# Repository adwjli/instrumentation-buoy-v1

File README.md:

# Instrumentation Buoy Data Logger

## Introduction

The client which I worked with in this project was working on a new concept to grow seaweed at an industrial scale (approximately 100km by 100km) in deep ocean waters tens of kilometres offshore. The seaweed plantation is kept afloat using buoys. One of the biggest challenge the client wanted to solve was how to keep the water near the surface of the ocean oxygenated to allow seaweed to grow. One idea was to use the motion of ocean waves to generate compressed air, which can be harnessed to pump air into the water to keep it oxygenated.

To aid in understanding how compressed air can be generated from ocean waves, a Instrumentation Buoy Data Logger was designed to measure various ocean metrics and record the data to a microSD card. The data logger had the following capabilities:
- Can measure water level and depth relative to the buoy.
- Can measure accelerations in all three spatial dimensions.
- Allows two pressure sensors to be connected to the board (via connectors located on the PCB)
- Designed to be completely solar powered. It is powered by an array of solar panels and a rechargeable 18650 Li-ion battery.
- A microSD card is used for data storage, but data transfer is done completely wirelessly using a XBee wireless module. The XBee module also allows over the air firmware updates. The solar-power and wireless capabilities of the data logger are necessary as the electronics will be permanently sealed away inside the buoy to ensure the electronics compartment is water-tight.

The data logger consists of two PCB assemblies sandwiched together. The smaller board is the Main Board. It contains the microcontroller, wireless module, and other digital electronics. The larger board is the Power Board which contains all the power electronics for solar charging. The entire PCB assembly is designed to be mounted in a prototype buoy, and deployed in the ocean to collect data.

The client has agreed to open source the designs.

## Gallery

## PCB Assemblies

## PCB Flats

## Copper Layers

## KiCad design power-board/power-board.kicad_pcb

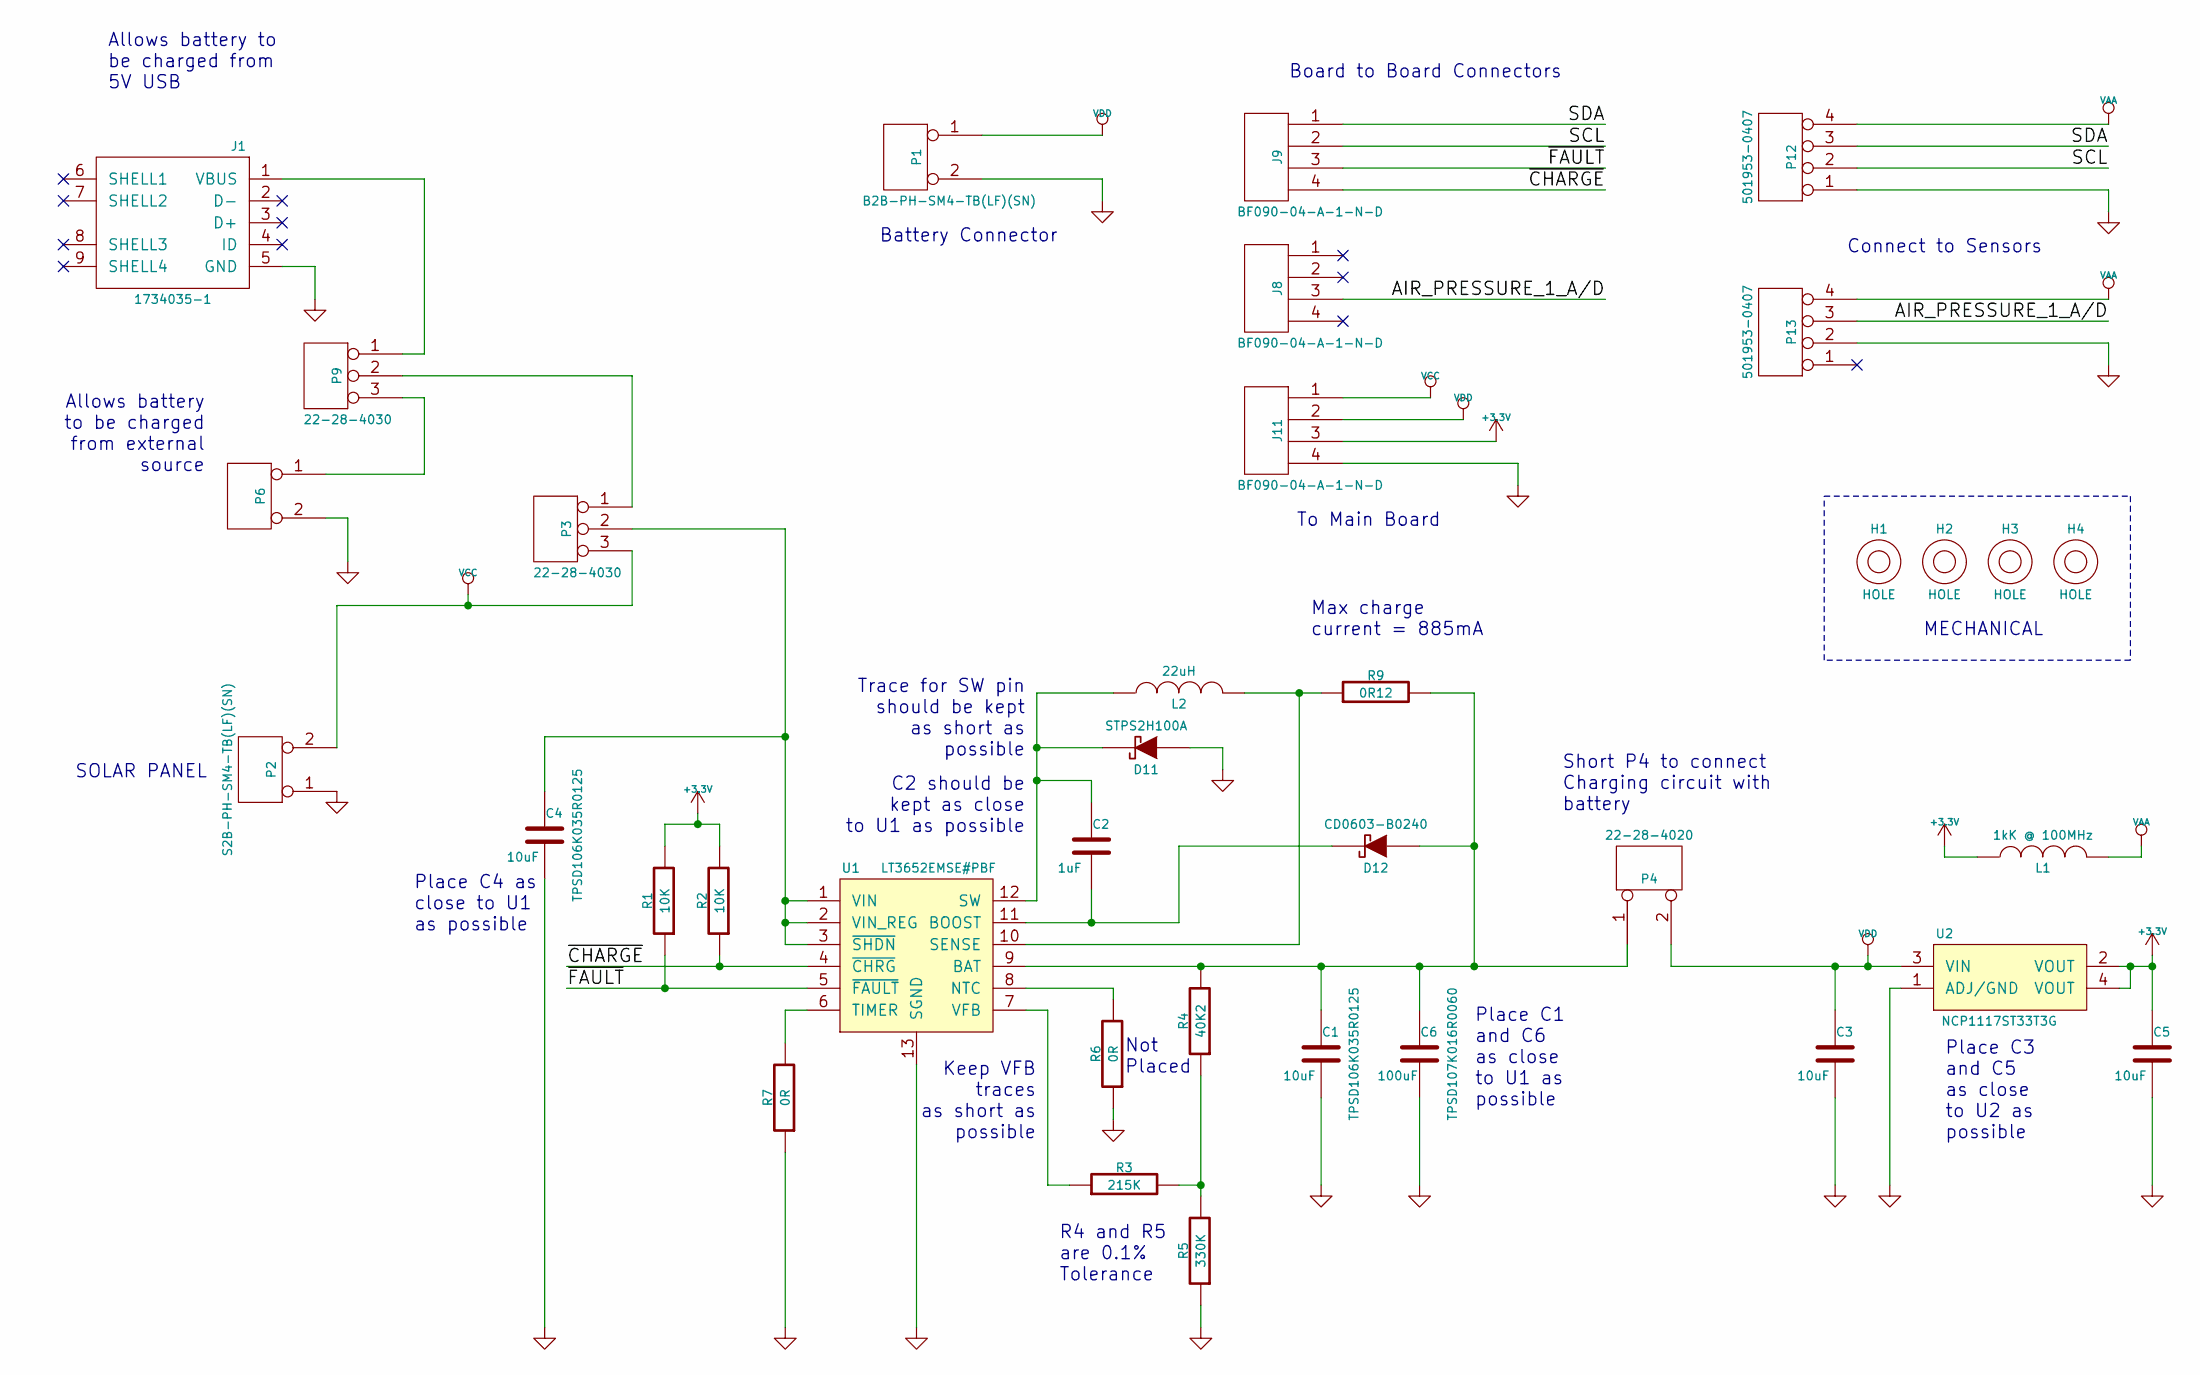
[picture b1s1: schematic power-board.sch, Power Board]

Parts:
C1, C4: ECS00053; EC2917; Manfacturer Part Number TPSD106K035R0125
C2: ECS00052; EC0603_C; Manfacturer Part Number GRM188R61H105KAALD
C3, C5: ECS00050; EC0805; Manfacturer Part Number GRM21BR61A106KE19L
C6: ECS00054; EC2917; Manfacturer Part Number TPSD107K016R0060
D11: ECS00095; ECDO-214AC(SMA); Manufacturer Part Number STPS2H100A
D12: ECS00037; EC0603_DIODE; Manufacturer Part Number CD0603-B0240
H1, H2, H3, H4: HOLE; HOLE_3.0MM
J1: ECS00066; ECUSBMINIB; Manufacturer Part Number 1734035-1
J8, J9, J11: ECS00059; ECS00059F; Manufacturer Part Number BF090-04-A-1-N-D
L1: ECS00074; EC0603_L; Manufacturer Part Number BLM18TG102TN1D
L2: ECS00071; ECS00071F; Manufacturer Part Number 46223C
P1, P6: ECS00067; ECS00067F; Manufacturer Part Number B2B-PH-SM4-TB(LF)(SN)
P2: ECS00007; ECS00007F; Manufacturer Part Number S2B-PH-SM4-TB(LF)(SN)
P3, P9: ECS00013; ECS00013F; Manufacturer Part Number 22-28-4030
P4: ECS00004; ECS00004F; Manufacturer Part Number 22-28-4020
P12, P13: ECS00068; ECS00068F; Manufacturer Part Number 501953-0407
R1, R2: ECS00045; EC0603; Manufacturer Part Number ERJ3GEYJ103V
R3: ECS00046; EC0603; Manufacturer Part Number ERJ3EKF2153V
R4: ECS00048; EC0603; Manufacturer Part Number ERA3ARB4022V
R5: ECS00047; EC0603; Manufacturer Part Number ERJ3EKF3303V
R6, R7: ECS00058; EC0603; Manufacturer Part Number ERJ3GEY0R00V
R9: ECS00055; EC1206; Manufacturer Part Number CRL1206-FW-R120ELF
U1: ECS00043; ECMSOP-12D; Manufacturer Part Number LT3652EMSE#PBF
U2: ECS00036; ECSOT223; Manufacturer Part Number NCP1117ST33T3G

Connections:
+3V3: C5.1, J11.3, L1.1, R1.2, R2.2, U2.2 (VOUT), U2.4 (VOUT)
/AIR_PRESSURE_1_A/D: J8.3, P13.3
/SCL: J9.2, P12.2
/SDA: J9.1, P12.3
/~CHARGE: J9.4, R2.1, U1.4 (~CHRG)
/~FAULT: J9.3, R1.1, U1.5 (~FAULT)
GND: C1.2, C3.2, C4.2, C5.2, C6.2, D11.1 (A), J1.5 (GND), J11.4, P1.2 (PM), P2.1, P6.2 (PM), P12.1, P13.2, R5.1, R6.1, R7.1, U1.13 (SGND), U2.1 (ADJ/GND)
unnamed: C1.1, C6.1, D12.1 (A), P4.1, R4.2, R9.2, U1.9 (BAT)
unnamed: C2.1, D11.2 (K), L2.1, U1.12 (SW)
unnamed: C2.2, D12.2 (K), U1.11 (BOOST)
unnamed: C4.1, P3.2 (PM), U1.1 (VIN), U1.2 (VIN_REG), U1.3 (~SHDN)
unnamed: J1.1 (VBUS), P9.1
unnamed: L2.2, R9.1, U1.10 (SENSE)
unnamed: P3.1, P9.2 (PM)
unnamed: P6.1, P9.3
unnamed: R3.1, U1.7 (VFB)
unnamed: R3.2, R4.1, R5.2
unnamed: R6.2, U1.8 (NTC)
unnamed: R7.2, U1.6 (TIMER)
VAA: L1.2, P12.4, P13.4
VCC: J11.1, P2.2 (PM), P3.3
VDD: C3.1, J11.2, P1.1, P4.2 (PM), U2.3 (VIN)

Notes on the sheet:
Battery Connector
R4 and R5 are 0.1% Tolerance
Not Placed
Max charge current = 885mA
Allows battery to be charged from 5V USB
Trace for SW pin should be kept as short as possible
Place C4 as close to U1 as possible
Place C1 and C6 as close to U1 as possible
Place C3 and C5 as close to U2 as possible
C2 should be kept as close to U1 as possible
Keep VFB traces as short as possible
Allows battery to be charged from external source
To Main Board
MECHANICAL
Connect to Sensors
Board to Board Connectors
SOLAR PANEL
Short P4 to connect Charging circuit with battery

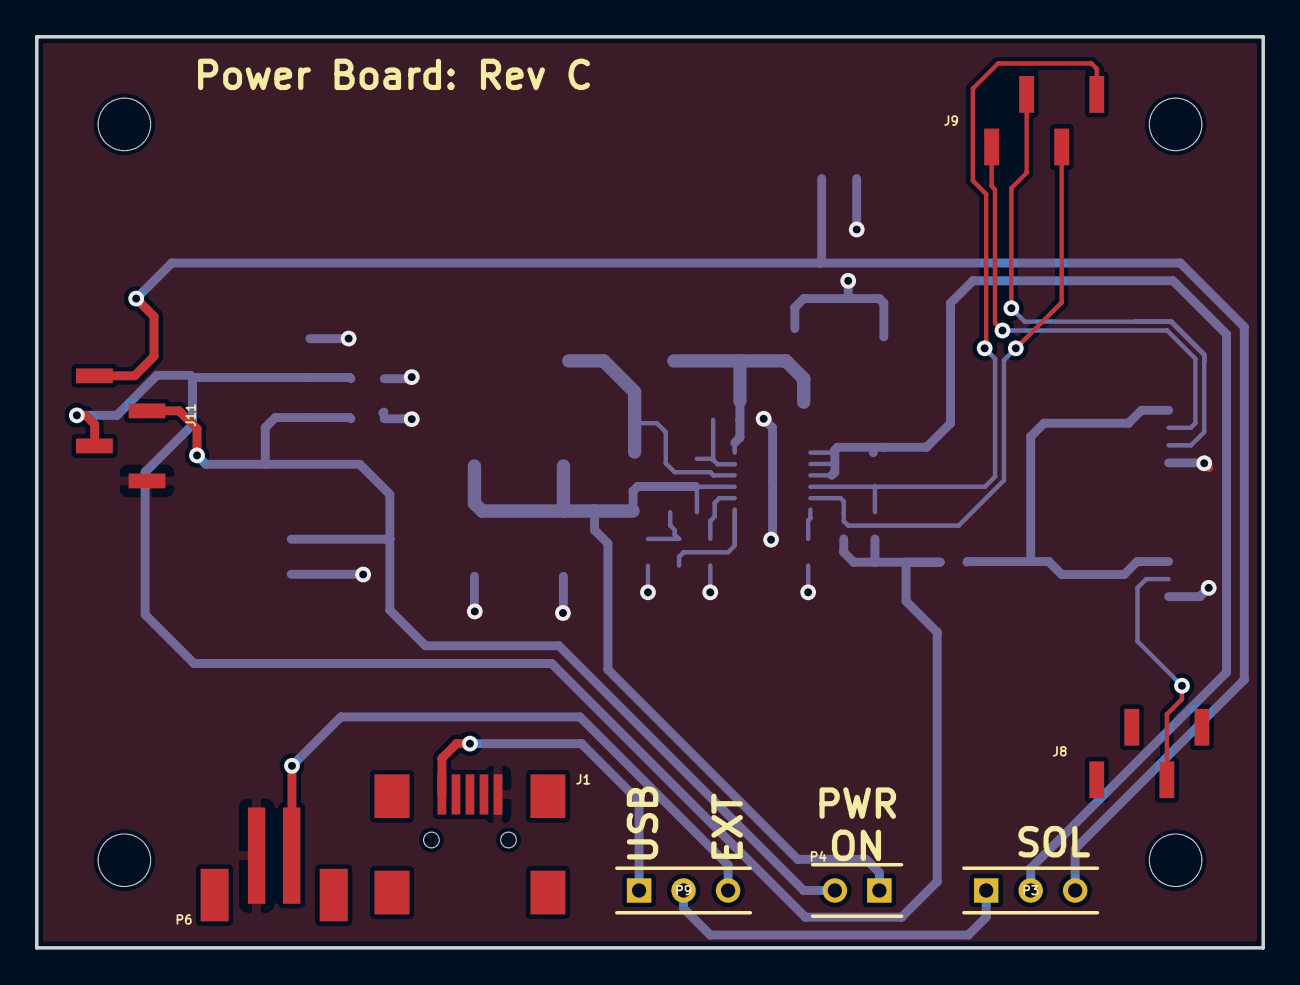
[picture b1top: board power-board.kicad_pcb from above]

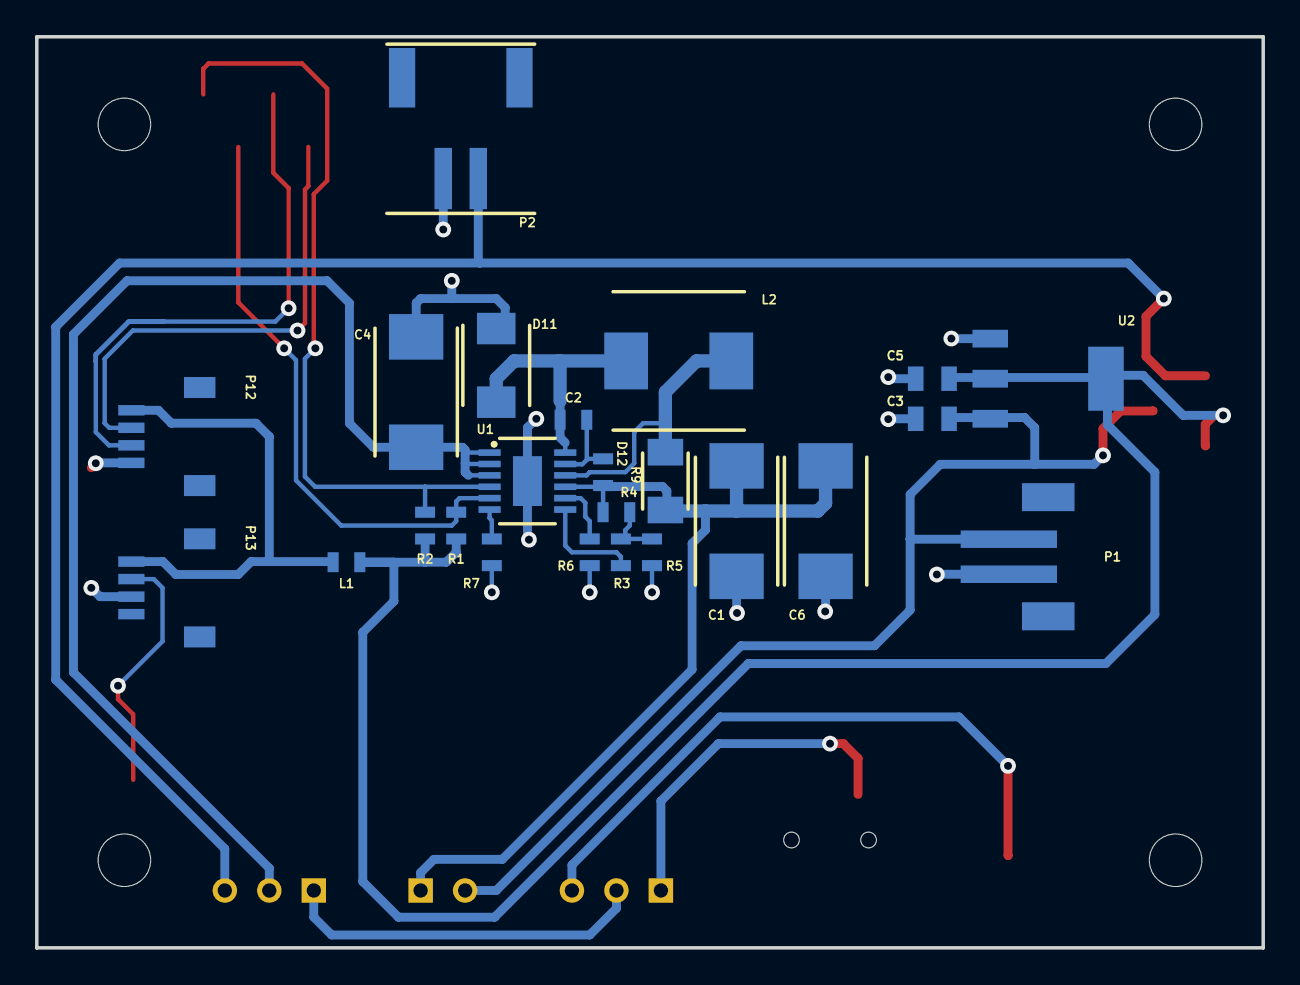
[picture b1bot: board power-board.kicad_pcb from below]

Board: 2 copper layers, 70.0 x 52.0 mm, 36 parts (24 on the bottom side), 22 nets.

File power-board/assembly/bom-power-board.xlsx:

Reference | Quantity | Internal Part Number | Component Value | Manufacturer | MPN | Part Description
C1 C4 | 2 | ECS00053 | 10uF | AVX | TPSD106K035R0125 | 10uF, 2917, 10%, 35V, Tantalum
C2 | 1 | ECS00052 | 1uF | Murata | GRM188R61H105KAALD | 1uF, 0603, 10%, 50V, X5R, Ceramic
C3 C5 | 2 | ECS00050 | 10uF | Murata | GRM21BR61A106KE19L | 10uF, 0805, 10%, 10V, X5R, Ceramic
C6 | 1 | ECS00054 | 100uF | AVX | TPSD107K016R0060 | 100uF, 2917, 10%, 16V, Tantalum
D11 | 1 | ECS00095 | ~ | ST Microelectronics | STPS2H100A | Schottky, Single, 2A, SMD
D12 | 1 | ECS00037 | ~ | Bourns | CD0603-B0240 | Schottky, Single, 0.1A, SMD
J1 | 1 | ECS00066 | ~ | TE Connectivity | 1734035-1 | Mini USB Type B, receptacle
J8 J9 J11 | 3 | ECS00059 | 4x1 | Global Connector Technology | BF090-04-A-1-N-D | 4-way, receptacle b-b, 2mm pitch, vertical, SMD, BF040 Series
L1 | 1 | ECS00074 | 1kK @ 100MHz | Murata | BLM18TG102TN1D | 1K @ 100MHz, 0603, 0.1A, 0R6
L2 | 1 | ECS00071 | 22uH | Murata | 46223C | 22uH, 1.8A, 0R12
P1 P6 | 2 | ECS00067 | 2x1 | JST | B2B-PH-SM4-TB(LF)(SN) | 2-way, header, 2mm pitch, vertical, SMD, PH Series
P12 P13 | 2 | ECS00068 | 4x1 | Molex | 501953-0407 | 4-way, header, 1mm pitch, right angle, SMD, Pico-Clasp 501953 Series
P2 | 1 | ECS00007 | 2x1 | JST | S2B-PH-SM4-TB(LF)(SN) | 2-way, header, 2mm pitch, right angle, SMD, PH Series
P4 | 1 | ECS00004 | 2x1 | Molex | 22-28-4020 | 2-way, header, 2.54mm pitch, vertical, through hole, KK Series
P9 P3 | 2 | ECS00013 | 3x1 | Molex | 22-28-4030 | 3-way, header, 2.54mm pitch, vertical, through hole, KK Series
R2 R1 | 2 | ECS00045 | 10K | Panasonic | ERJ3GEYJ103V | 10K, 0603, 5%, 0.1W, Thick Film
R3 | 1 | ECS00046 | 215K | Panasonic | ERJ3EKF2153V | 215K, 0603, 1%, 0.1W, Thick Film
R4 | 1 | ECS00048 | 40K2 | Panasonic | ERA3ARB4022V | 40K2, 0603, 0.1%, 0.1W, Thin Film
R5 | 1 | ECS00047 | 330K | Panasonic | ERJ3EKF3303V | 330K, 0603, 1%, 0.1W, Thick Film
R7 R6 | 2 | ECS00058 | 0R | Panasonic | ERJ3GEY0R00V | 0R, 0603, 0.1W, Jumper
R9 | 1 | ECS00055 | 0R12 | Bourns | CRL1206-FW-R120ELF | 0R12, 1206, 1%, 0.25W, Thick Film
U1 | 1 | ECS00043 | ~ | Linear Technology | LT3652EMSE#PBF | Switch Mode Charge Controller with MPPT
U2 | 1 | ECS00036 | ~ | On Semiconductor | NCP1117ST33T3G | 3.3V Linear Regulator

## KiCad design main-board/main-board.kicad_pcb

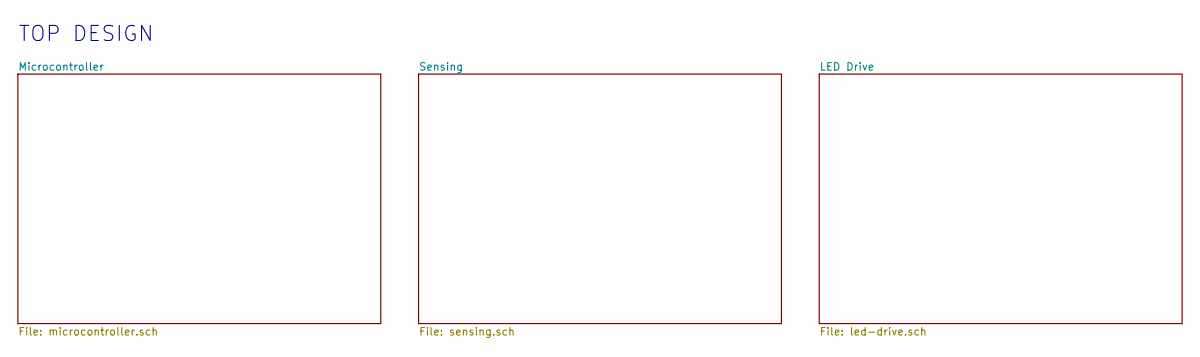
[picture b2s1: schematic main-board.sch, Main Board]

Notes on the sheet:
TOP DESIGN

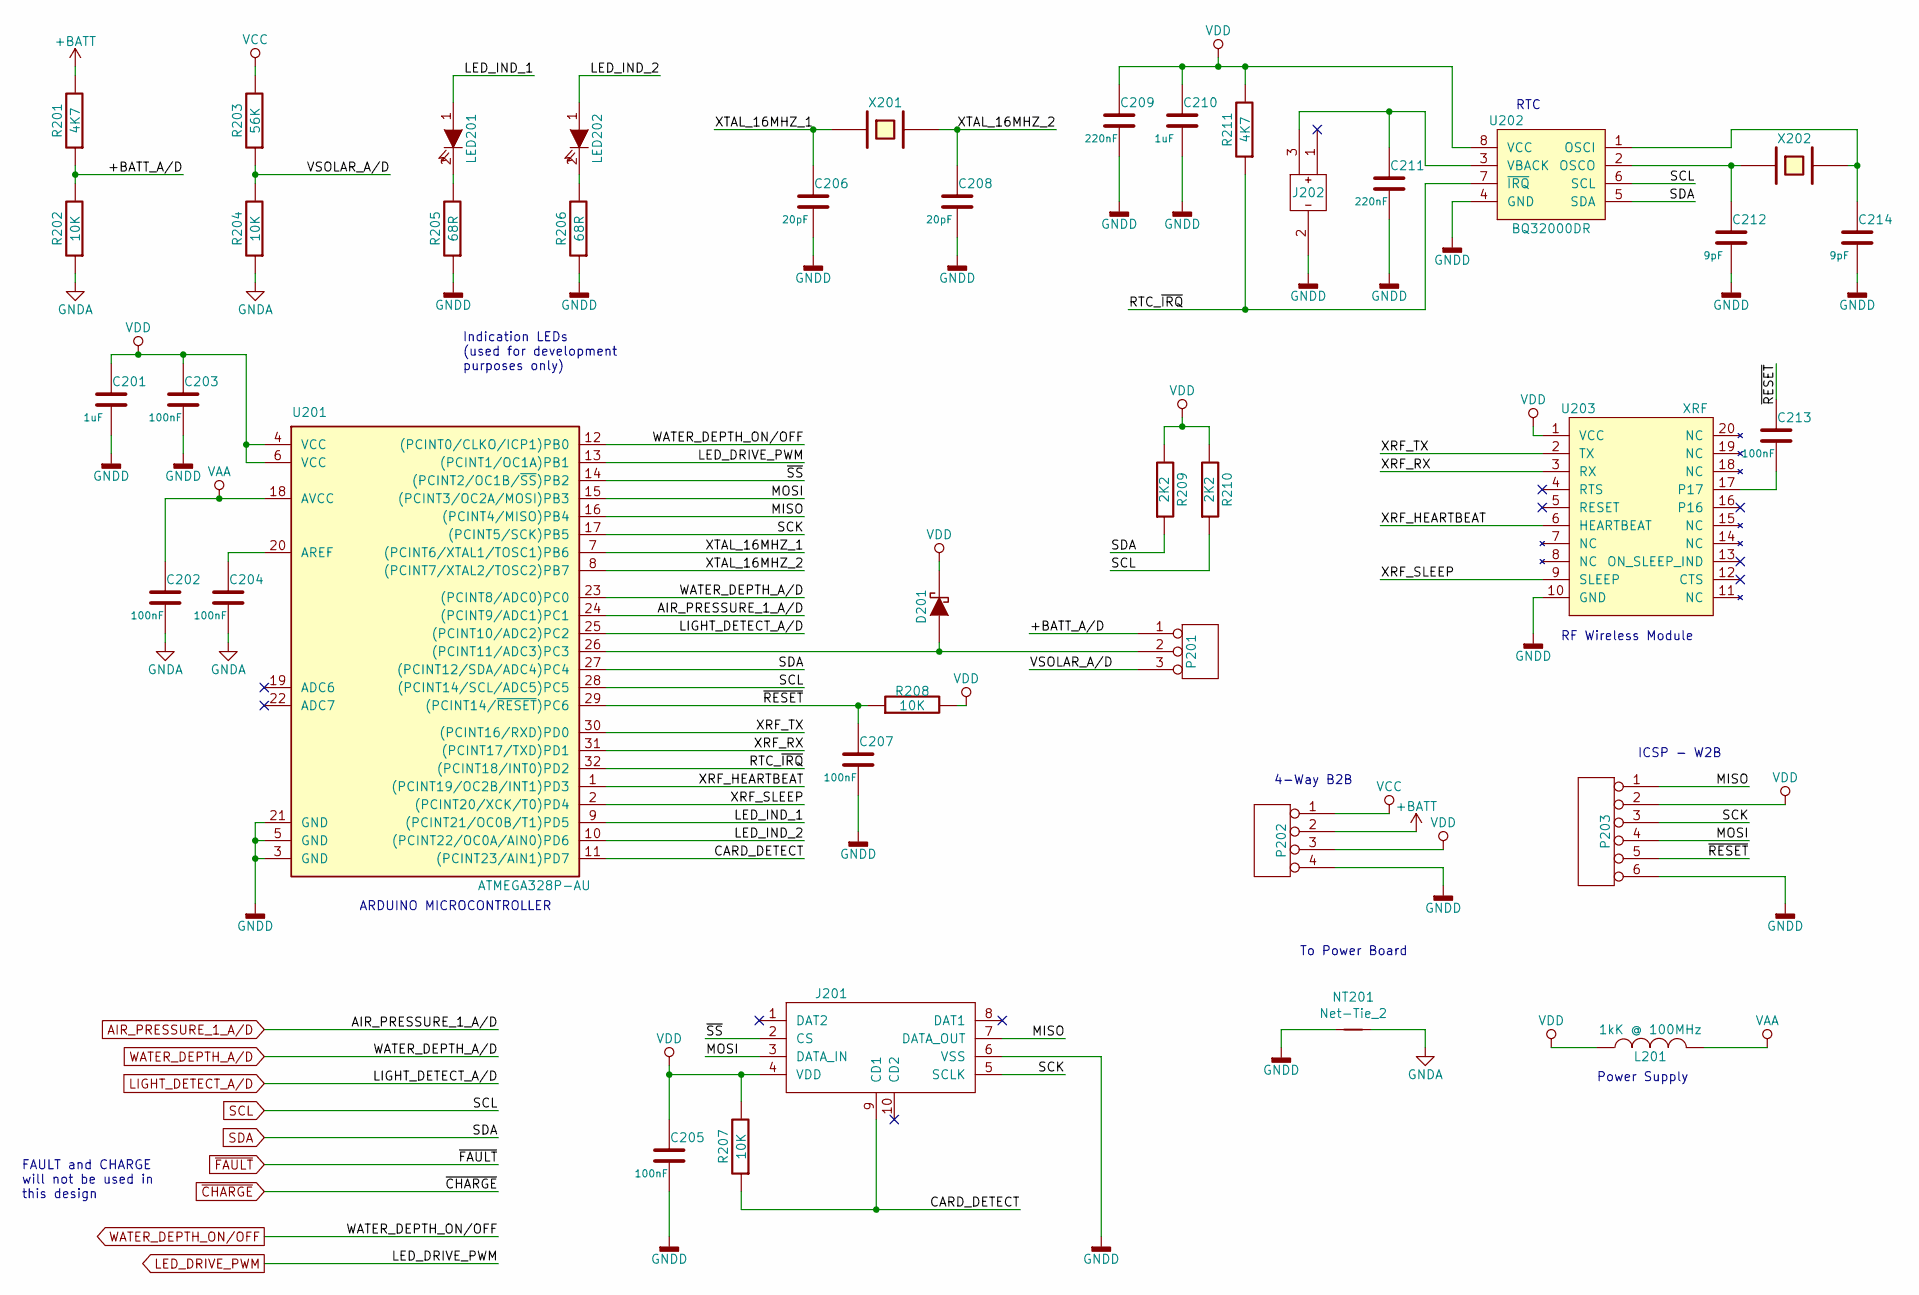
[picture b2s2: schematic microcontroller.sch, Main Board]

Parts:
C201, C210: ECS00052; EC0603_C; Manfacturer Part Number GRM188R61H105KAALD
C202, C203, C204, C205, C207, C213: ECS00075; EC0603_C; Manfacturer Part Number GRM188R71C104KA01D
C206, C208: ECS00077; EC0603_C; Manfacturer Part Number C0603C200J5GACTU
C209, C211: ECS00078; EC0603_C; Manfacturer Part Number GRM188R71A224KA01D
C212, C214: ECS00076; EC0603_C; Manfacturer Part Number MC0603N9R0D500CT
D201: ECS00037; EC0603_DIODE; Manufacturer Part Number CD0603-B0240
J201: ECS00065; ECS00065F; Manufacturer Part Number 114-00841-68
J202: ECS00094; ECS00094F; Manufacturer Part Number BK-868
L201: ECS00074; EC0603_L; Manufacturer Part Number BLM18TG102TN1D
LED201, LED202: ECS00035; EC0603_LED; Manufacturer Part Number SML-310VTT86L
NT201: Net-Tie_2; NetTie-2_SMD_Pad0.5mm
P201: ECS00013; ECS00013F; Manufacturer Part Number 22-28-4030
P202: ECS00029; ECS00029F; Manufacturer Part Number BF040-04A-B2-0400-0260-0483-LD
P203: ECS00015; ECS00015F; Manufacturer Part Number 87437-0673
R201, R211: ECS00086; EC0603; Manufacturer Part Number CR0603-FX-4701ELF
R202, R204, R207, R208: ECS00045; EC0603; Manufacturer Part Number ERJ3GEYJ103V
R203: ECS00085; EC0603; Manufacturer Part Number CRCW060356K0FKEAHP
R205, R206: ECS00081; EC0603; Manufacturer Part Number CR0603-FX-68R0ELF
R209, R210: ECS00084; EC0603; Manufacturer Part Number MC0063W060312K2
U201: ECS00017; ECTQFP-32; Manufacturer Part Number ATMEGA328P-AU
U202: ECS00032; ECSOIC-8; Manufacturer Part Number BQ32000DR
U203: ECA00002; ECA00002F; Manufacturer Part Number XRF
X201: ECS00006; ECS00006F; Manufacturer Part Number FOXSDLF/160-20
X202: ECS00005; ECS00005F; Manufacturer Part Number CC4V-T1A 32.768KHZ +-20PPM 9PF

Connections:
+BATT: P202.2, R201.2; also elsewhere on the board
/Microcontroller/+BATT_A/D: P201.1, R201.1, R202.2
/Microcontroller/CARD_DETECT: J201.9 (CD1), R207.1, U201.11 ((PCINT23/AIN1)PD7)
/Microcontroller/LED_IND_1: LED201.1 (A), U201.9 ((PCINT21/OC0B/T1)PD5)
/Microcontroller/LED_IND_2: LED202.1 (A), U201.10 ((PCINT22/OC0A/AIN0)PD6)
/Microcontroller/MISO: J201.7 (DATA_OUT), P203.1, U201.16 ((PCINT4/MISO)PB4)
/Microcontroller/MOSI: J201.3 (DATA_IN), P203.4, U201.15 ((PCINT3/OC2A/MOSI)PB3)
/Microcontroller/RTC_~IRQ: R211.1, U201.32 ((PCINT18/INT0)PD2), U202.7 (~IRQ)
/Microcontroller/SCK: J201.5 (SCLK), P203.3, U201.17 ((PCINT5/SCK)PB5)
/Microcontroller/VSOLAR_A/D: P201.3, R203.1, R204.2
/Microcontroller/XRF_HEARTBEAT: U201.1 ((PCINT19/OC2B/INT1)PD3), U203.6 (HEARTBEAT)
/Microcontroller/XRF_RX: U201.31 ((PCINT17/TXD)PD1), U203.3 (RX)
/Microcontroller/XRF_SLEEP: U201.2 ((PCINT20/XCK/T0)PD4), U203.9 (SLEEP)
/Microcontroller/XRF_TX: U201.30 ((PCINT16/RXD)PD0), U203.2 (TX)
/Microcontroller/XTAL_16MHZ_1: C206.1, U201.7 ((PCINT6/XTAL1/TOSC1)PB6), X201.1
/Microcontroller/XTAL_16MHZ_2: C208.1, U201.8 ((PCINT7/XTAL2/TOSC2)PB7), X201.2
/Microcontroller/~RESET: C207.1, C213.1, P203.5, R208.1, U201.29 ((PCINT14/~RESET~)PC6)
/Microcontroller/~SS: J201.2 (CS), U201.14 ((PCINT2/OC1B/~SS~)PB2)
AIR_PRESSURE_1_A/D: U201.24 ((PCINT9/ADC1)PC1); also elsewhere on the board
GNDA: C202.2, C204.2, NT201.2, R202.1, R204.1; also elsewhere on the board
GNDD: C201.2, C203.2, C205.2, C206.2, C207.2, C208.2, C209.2, C210.2, C211.2, C212.2, C214.2, J201.6 (VSS), J202.2 (-), NT201.1, P202.4, P203.6, R205.1, R206.1, U201.3 (GND), U201.5 (GND), U201.21 (GND), U202.4 (GND), U203.10 (GND); also elsewhere on the board
LED_DRIVE_PWM: U201.13 ((PCINT1/OC1A)PB1); also elsewhere on the board
LIGHT_DETECT_A/D: U201.25 ((PCINT10/ADC2)PC2); also elsewhere on the board
unnamed: C204.1, U201.20 (AREF)
unnamed: C211.1, J202.3 (+), U202.3 (VBACK)
unnamed: C212.1, U202.2 (OSCO), X202.1
unnamed: C213.2, U203.17
unnamed: C214.1, U202.1 (OSCI), X202.2
unnamed: D201.1 (A), P201.2 (PM), U201.26 ((PCINT11/ADC3)PC3)
unnamed: LED201.2 (K), R205.2
unnamed: LED202.2 (K), R206.2
SCL: R210.1, U201.28 ((PCINT14/SCL/ADC5)PC5), U202.6 (SCL); also elsewhere on the board
SDA: R209.1, U201.27 ((PCINT12/SDA/ADC4)PC4), U202.5 (SDA); also elsewhere on the board
VAA: C202.1, L201.2, U201.18 (AVCC); also elsewhere on the board
VCC: P202.1, R203.2
VDD: C201.1, C203.1, C205.1, C209.1, C210.1, D201.2 (K), J201.4 (VDD), L201.1, P202.3, P203.2, R207.2, R208.2, R209.2, R210.2, R211.2, U201.4 (VCC), U201.6 (VCC), U202.8 (VCC), U203.1 (VCC); also elsewhere on the board
WATER_DEPTH_A/D: U201.23 ((PCINT8/ADC0)PC0); also elsewhere on the board
WATER_DEPTH_ON/OFF: U201.12 ((PCINT0/CLKO/ICP1)PB0); also elsewhere on the board

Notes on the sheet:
RTC
RF Wireless Module
ICSP - W2B
4-Way B2B
ARDUINO MICROCONTROLLER
To Power Board
Power Supply
Indication LEDs (used for development purposes only)
FAULT and CHARGE will not be used in this design

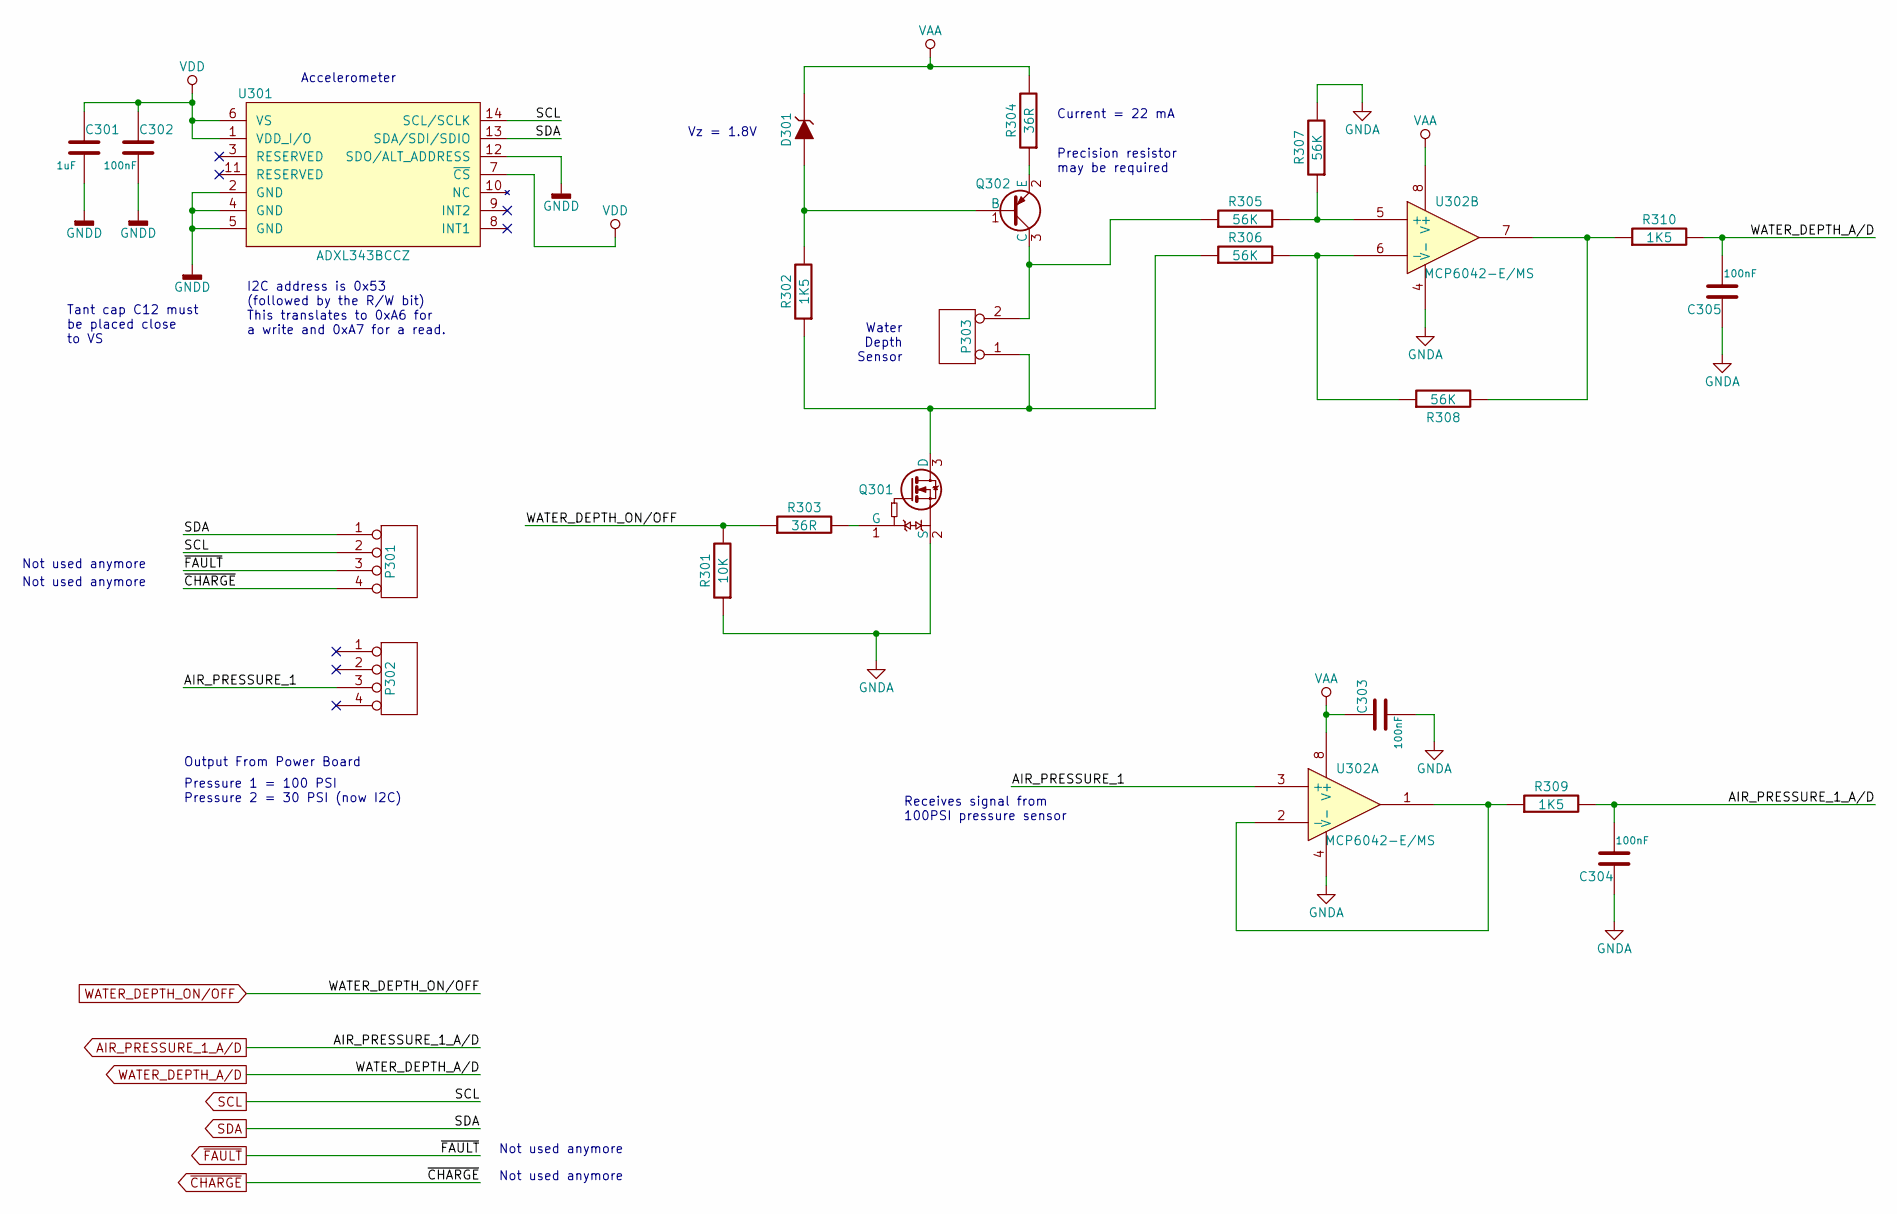
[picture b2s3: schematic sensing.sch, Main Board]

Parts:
C301: ECS00052; EC0603_C; Manfacturer Part Number GRM188R61H105KAALD
C302, C303, C304, C305: ECS00075; EC0603_C; Manfacturer Part Number GRM188R71C104KA01D
D301: ECS00072; ECS00072F; Manufacturer Part Number MMSZ4678T1G
P301, P302: ECS00029; ECS00029F; Manufacturer Part Number BF040-04A-B2-0400-0260-0483-LD
P303: ECS00067; ECS00067F; Manufacturer Part Number B2B-PH-SM4-TB(LF)(SN)
Q301: ECS00087; ECSOT416; Manufacturer Part Number NTA4153NT1G
Q302: ECS00073; ECSOT323; Manufacturer Part Number BC857BW,115
R301: ECS00045; EC0603; Manufacturer Part Number ERJ3GEYJ103V
R302, R309, R310: ECS00083; EC0603; Manufacturer Part Number CR0603-FX-1501ELF
R303, R304: ECS00080; EC0603; Manufacturer Part Number CRCW060336R0FKEA
R305, R306, R307, R308: ECS00085; EC0603; Manufacturer Part Number CRCW060356K0FKEAHP
U301: ECS00016; ECS00016F; Manufacturer Part Number ADXL343BCCZ
U302: ECS00030; ECMSOP-8; Manufacturer Part Number MCP6042-E/MS

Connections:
/Sensing/AIR_PRESSURE_1: P302.3, U302.3 (+)
AIR_PRESSURE_1_A/D: C304.2, R309.2; also elsewhere on the board
GNDA: C303.2, C304.1, C305.1, Q301.2 (S), R301.1, R307.2, U302.4 (V-); also elsewhere on the board
GNDD: C301.2, C302.2, U301.2 (GND), U301.4 (GND), U301.5 (GND), U301.12 (SDO/ALT_ADDRESS); also elsewhere on the board
unnamed: D301.2 (A), Q302.1 (B), R302.2
unnamed: P303.1, Q301.3 (D), R302.1, R306.1
unnamed: P303.2 (PM), Q302.3 (C), R305.1
unnamed: Q301.1 (G), R303.2
unnamed: Q302.2 (E), R304.1
unnamed: R305.2, R307.1, U302.5 (+)
unnamed: R306.2, R308.1, U302.6 (-)
unnamed: R308.2, R310.1, U302.7
unnamed: R309.1, U302.1, U302.2 (-)
SCL: P301.2, U301.14 (SCL/SCLK); also elsewhere on the board
SDA: P301.1, U301.13 (SDA/SDI/SDIO); also elsewhere on the board
VAA: C303.1, D301.1 (K), R304.2, U302.8 (V+); also elsewhere on the board
VDD: C301.1, C302.1, U301.1 (VDD_I/O), U301.6 (VS), U301.7 (~CS); also elsewhere on the board
WATER_DEPTH_A/D: C305.2, R310.2; also elsewhere on the board
WATER_DEPTH_ON/OFF: R301.2, R303.1; also elsewhere on the board

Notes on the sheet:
Accelerometer
I2C address is 0x53 (followed by the R/W bit) This translates to 0xA6 for a write and 0xA7 for a read.
Precision resistor may be required
Water Depth Sensor
Current = 22 mA
Vz = 1.8V
Output From Power Board
Pressure 1 = 100 PSI Pressure 2 = 30 PSI (now I2C)
Tant cap C12 must be placed close to VS
Receives signal from 100PSI pressure sensor
Not used anymore

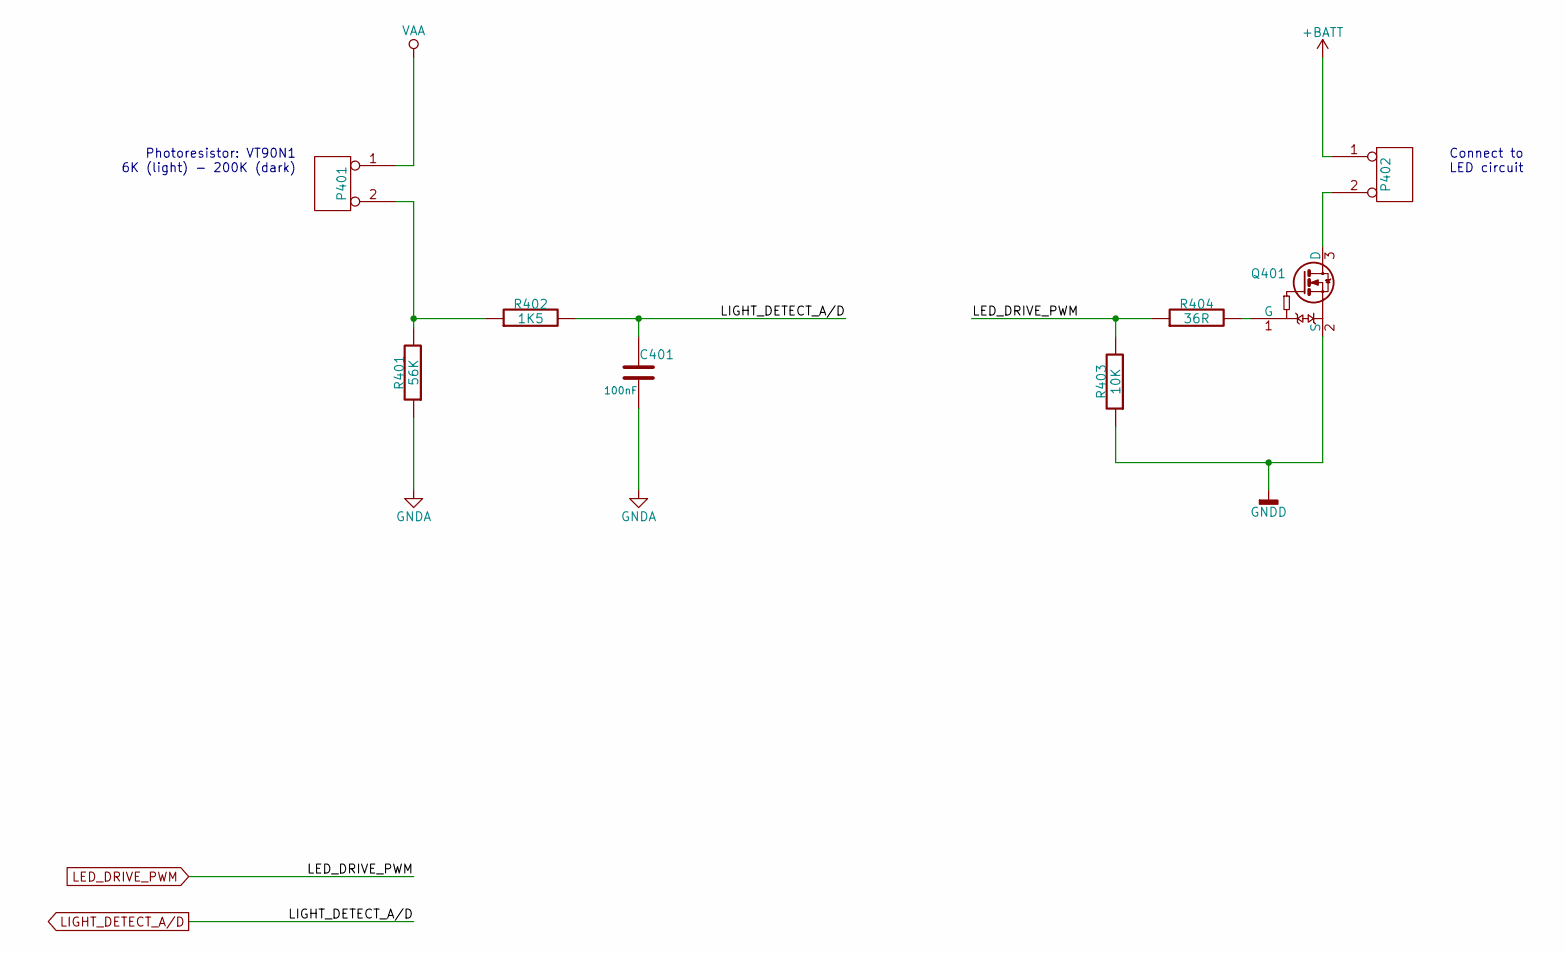
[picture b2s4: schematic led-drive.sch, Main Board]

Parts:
C401: ECS00075; EC0603_C; Manfacturer Part Number GRM188R71C104KA01D
P401, P402: ECS00067; ECS00067F; Manufacturer Part Number B2B-PH-SM4-TB(LF)(SN)
Q401: ECS00087; ECSOT416; Manufacturer Part Number NTA4153NT1G
R401: ECS00085; EC0603; Manufacturer Part Number CRCW060356K0FKEAHP
R402: ECS00083; EC0603; Manufacturer Part Number CR0603-FX-1501ELF
R403: ECS00045; EC0603; Manufacturer Part Number ERJ3GEYJ103V
R404: ECS00080; EC0603; Manufacturer Part Number CRCW060336R0FKEA

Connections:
+BATT: P402.1; also elsewhere on the board
GNDA: C401.2, R401.1; also elsewhere on the board
GNDD: Q401.2 (S), R403.1; also elsewhere on the board
LED_DRIVE_PWM: R403.2, R404.1; also elsewhere on the board
LIGHT_DETECT_A/D: C401.1, R402.2; also elsewhere on the board
unnamed: P401.2 (PM), R401.2, R402.1
unnamed: P402.2 (PM), Q401.3 (D)
unnamed: Q401.1 (G), R404.2
VAA: P401.1; also elsewhere on the board

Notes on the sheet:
Connect to LED circuit
Photoresistor: VT90N1 6K (light) - 200K (dark)
